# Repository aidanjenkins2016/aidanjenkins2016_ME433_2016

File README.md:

# aidanjenkins2016_ME433_2016
# March 31, 2016
#The repository will help with sharing my code as well as letting me roll back changes
#updates

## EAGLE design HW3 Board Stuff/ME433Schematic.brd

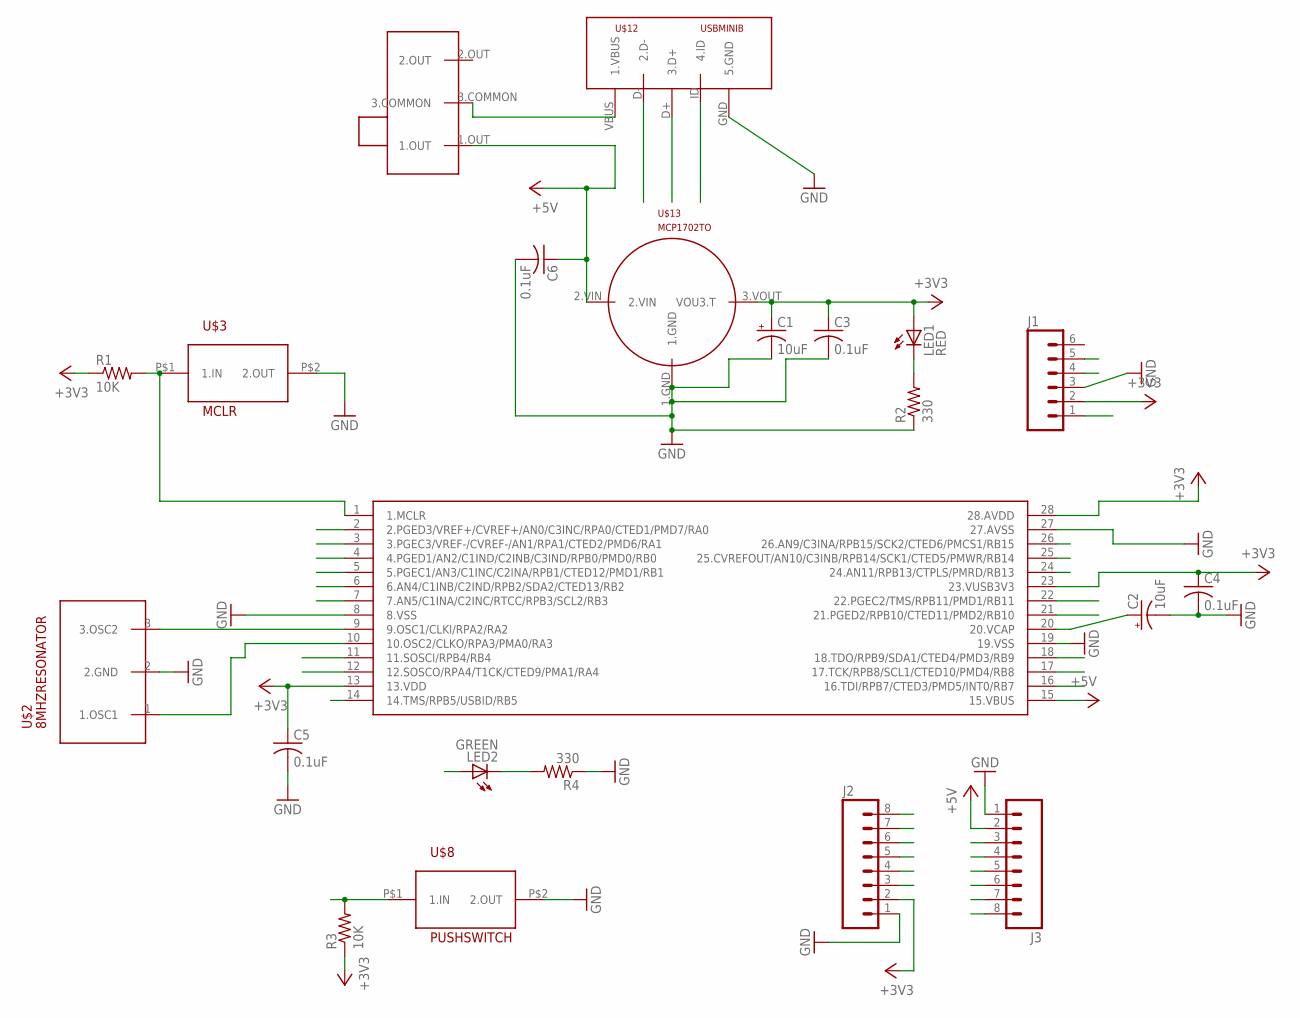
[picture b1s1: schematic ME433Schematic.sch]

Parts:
C1, C2: 10uF; B45181B
C3, C4, C5, C6: 0.1uF; C025-025X050
J1: M06SILK_FEMALE_PTH; 1X06
J2, J3: M08; 1X08_ROUND
LED1: RED; LED3MM
LED2: GREEN; LED3MM
R1, R3: 10K; 0207/10
R2, R4: 330; 0207/10
U$1: PIC32MX250F128B; DIL28-3
U$2: 8MHZRESONATOR; 1X03
U$3: MCLR; SWITCH
U$8: PUSHSWITCH; SWITCH
U$12: USBMINIB; USB-MB-H
U$13: MCP1702TO; TO92
U$18: SLIDESWITCH; SPDTSLIDE

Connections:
+3V3: C1.+, C3.1, C4.1, C5.1, J1.2, J2.2, LED1.A (1.+), R1.1, R3.1, U$1.13 (13.VDD), U$1.23 (23.VUSB3V3), U$1.28 (28.AVDD), U$13.3.VOUT (VOU3.T)
+5V: C6.1, J3.2, U$1.15 (15.VBUS), U$13.2.VIN, U$18.1.OUT
A0: J2.8, U$1.2 (2.PGED3/VREF+/CVREF+/AN0/C3INC/RPA0/CTE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)
A1: J2.7, U$1.3 (3.PGEC3/VREF-/CVREF-/AN1/RPA1/CTED2/PMD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)
A4: J2.3, LED2.A (1.+), U$1.12 (12.SOSCO/RPA4/T1CK/CTED9/PMA1/RA4)
B2: J2.6, U$1.6 (6.AN4/C1INB/C2IND/RPB2/SDA2/CTED13/RB2)
B3: J2.5, U$1.7 (7.AN5/C1INA/C2INC/RTCC/RPB3/SCL2/RB3)
B4: J2.4, R3.2, U$1.11 (11.SOSCI/RPB4/RB4), U$8.P$1 (1.IN)
B7: J3.3, U$1.16 (16.TDI/RPB7/CTED3/PMD5/INT0/RB7)
B8: J3.4, U$1.17 (17.TCK/RPB8/SCL1/CTED10/PMD4/RB8)
B9: J3.5, U$1.18 (18.TDO/RPB9/SDA1/CTED4/PMD3/RB9)
B13: J3.6, U$1.24 (24.AN11/RPB13/CTPLS/PMRD/RB13)
B14: J3.7, U$1.25 (25.CVREFOUT/AN10/C3INB/RPB14/SCK1/CTED5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)
B15: J3.8, U$1.26 (26.AN9/C3INA/RPB15/SCK2/CTED6/PMCS1/RB15)
D+: U$1.21 (21.PGED2/RPB10/CTED11/PMD2/RB10), U$12.D+ (3.D+)
D-: U$1.22 (22.PGEC2/TMS/RPB11/PMD1/RB11), U$12.D- (2.D-)
GND: C1.-, C2.-, C3.2, C4.2, C5.2, C6.2, J1.3, J2.1, J3.1, R2.1, R4.1, U$1.8 (8.VSS), U$1.19 (19.VSS), U$1.27 (27.AVSS), U$2.2 (2.GND), U$3.P$2 (2.OUT), U$8.P$2 (2.OUT), U$12.GND (5.GND), U$13.1.GND
ID: U$1.14 (14.TMS/RPB5/USBID/RB5), U$12.ID (4.ID)
MCLR: J1.1, R1.2, U$1.1 (1.MCLR), U$3.P$1 (1.IN)
unnamed: U$12.VBUS (1.VBUS), U$18.3.COMMON
unnamed: U$1.9 (9.OSC1/CLKI/RPA2/RA2), U$2.3 (3.OSC2)
unnamed: U$1.10 (10.OSC2/CLKO/RPA3/PMA0/RA3), U$2.1 (1.OSC1)
unnamed: C2.+, U$1.20 (20.VCAP)
unnamed: LED2.K (2.-), R4.2
unnamed: LED1.K (2.-), R2.2
PEGC1: J1.5, U$1.5 (5.PGEC1/AN3/C1INC/C2INA/RPB1/CTED12/PMD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)
PEGD1: J1.4, U$1.4 (4.PGED1/AN2/C1IND/C2INB/C3IND/RPB0/PMD0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)

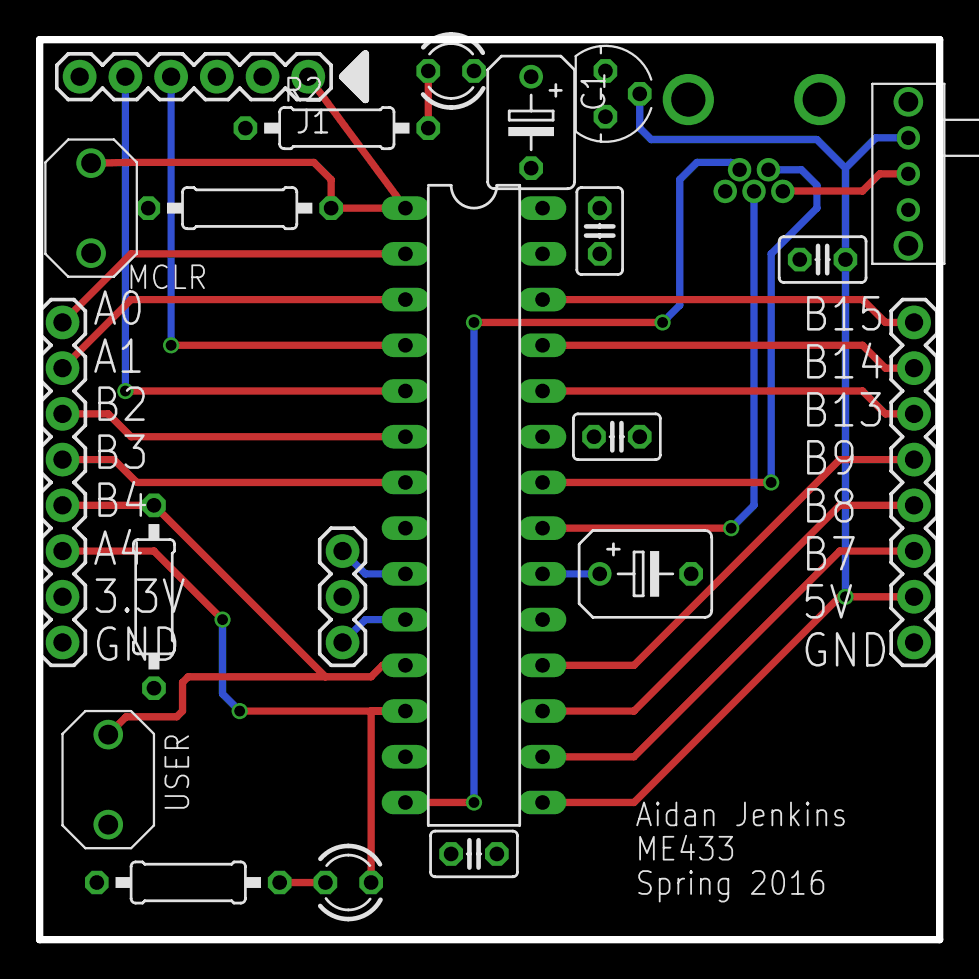
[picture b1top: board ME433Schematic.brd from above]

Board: 2 copper layers, 50.0 x 50.0 mm, 22 parts (0 on the bottom side), 27 nets.

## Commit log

2016-04-01 HW1 photos
2016-04-04 Upload 04042016
2016-04-05 Main.c code working and screenshot of timing
2016-04-07 partial eagle library sub
2016-04-07 pic added to library
2016-04-11 added sparkfun, led, and resistor libraries
2016-04-11 copied in the correct subsets of the appropriate libraries
2016-04-11 usb and regulator created
2016-04-11 added 10 uf and 0.1 uf capacitors
2016-04-12 Library done, partial schematic completion
2016-04-13 need to know if power plane is good idea re capacitors
2016-04-14 Ready to be checked before order, looked good on Seeed, holes were off by 10x-100x in Mayhew labs
2016-04-14 Board updated ready to review
2016-04-19 adding hw4 in progress
2016-04-25 Working on I2C and SPI
2016-04-25 I2C sending data to expander, but LED toggle not consistent
2016-04-25 I2C still buggy, some SPI code added, but not compiling
2016-04-25 SPI added and compiling, not working on nScope
2016-05-01 I2C working
2016-05-01 I2C wokring, SPI some data and clock being sent, needs work
2016-05-16 post design comp catch up. USB compiling
2016-05-16 added CDC compiling
2016-05-17 HW9 android hello world and slider
2016-05-19 HW11 done
2016-05-19 rearrange and HW10
2016-05-22 HW5 LCD hello world
2016-06-04 Robot parts, new CDC
2016-06-04 New camera app. Slider for threshold and visual calibration mode
2016-06-04 Android CDC app
2016-06-09 forgot to upload earlier
2016-06-10 just a few more files i forgot to add
2016-06-10 Added HW16
2016-06-10 put all board files in a folder
